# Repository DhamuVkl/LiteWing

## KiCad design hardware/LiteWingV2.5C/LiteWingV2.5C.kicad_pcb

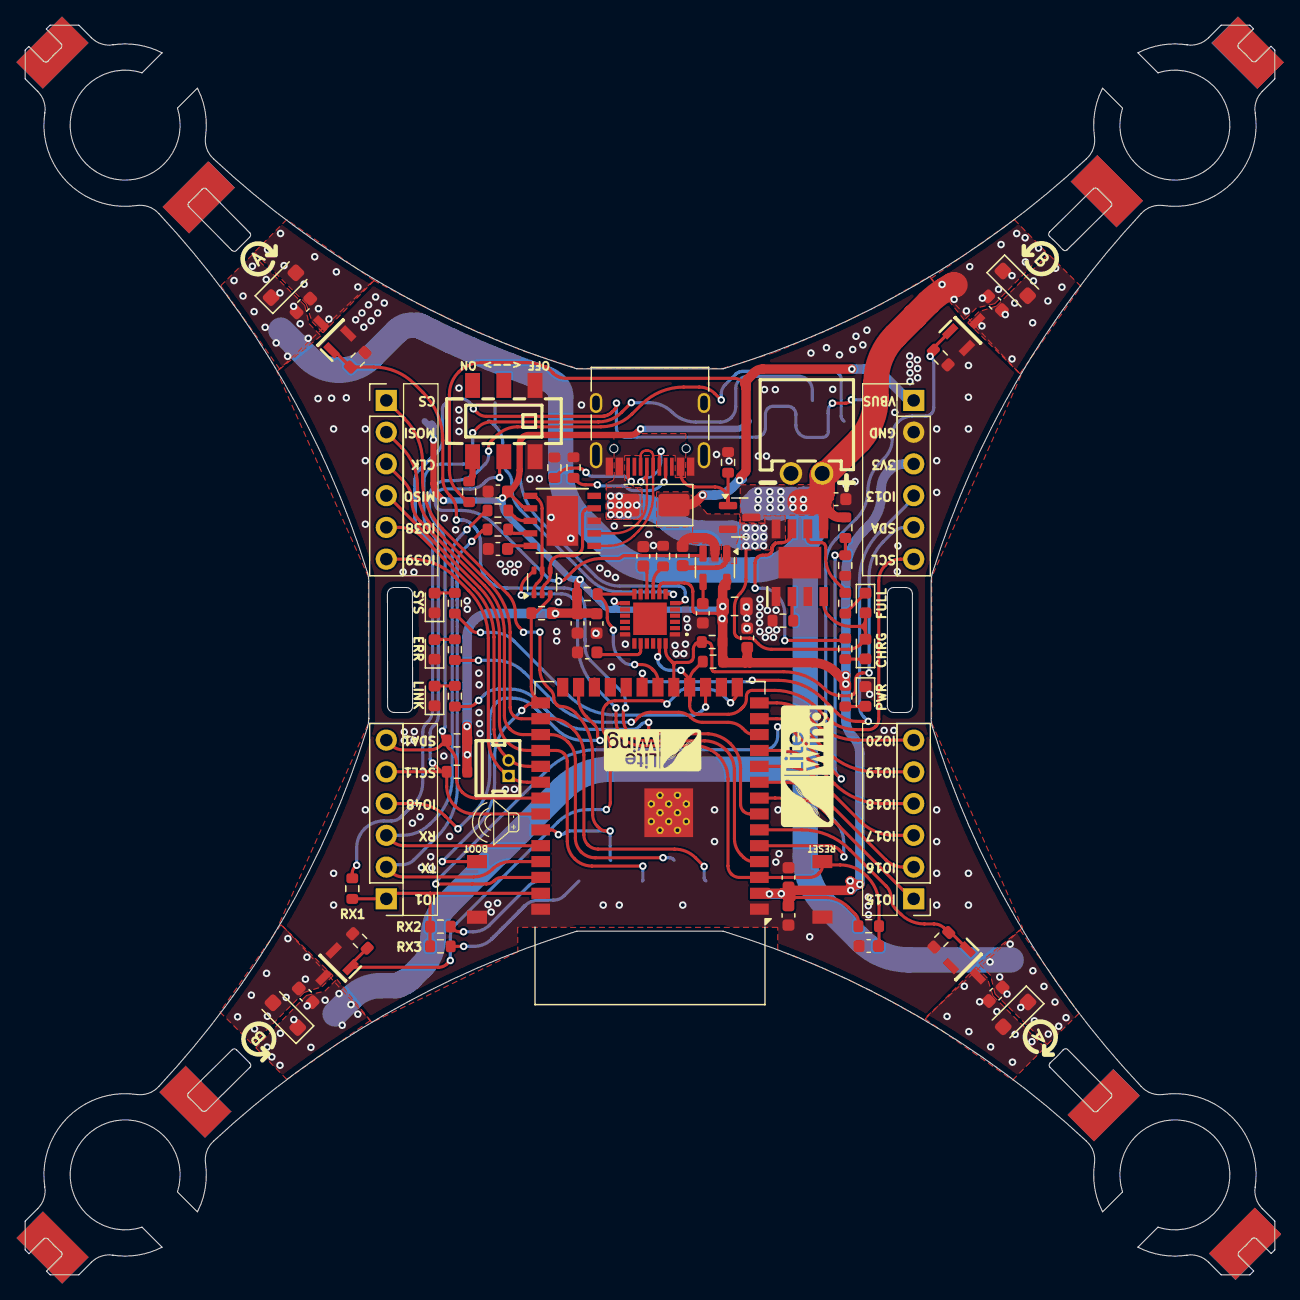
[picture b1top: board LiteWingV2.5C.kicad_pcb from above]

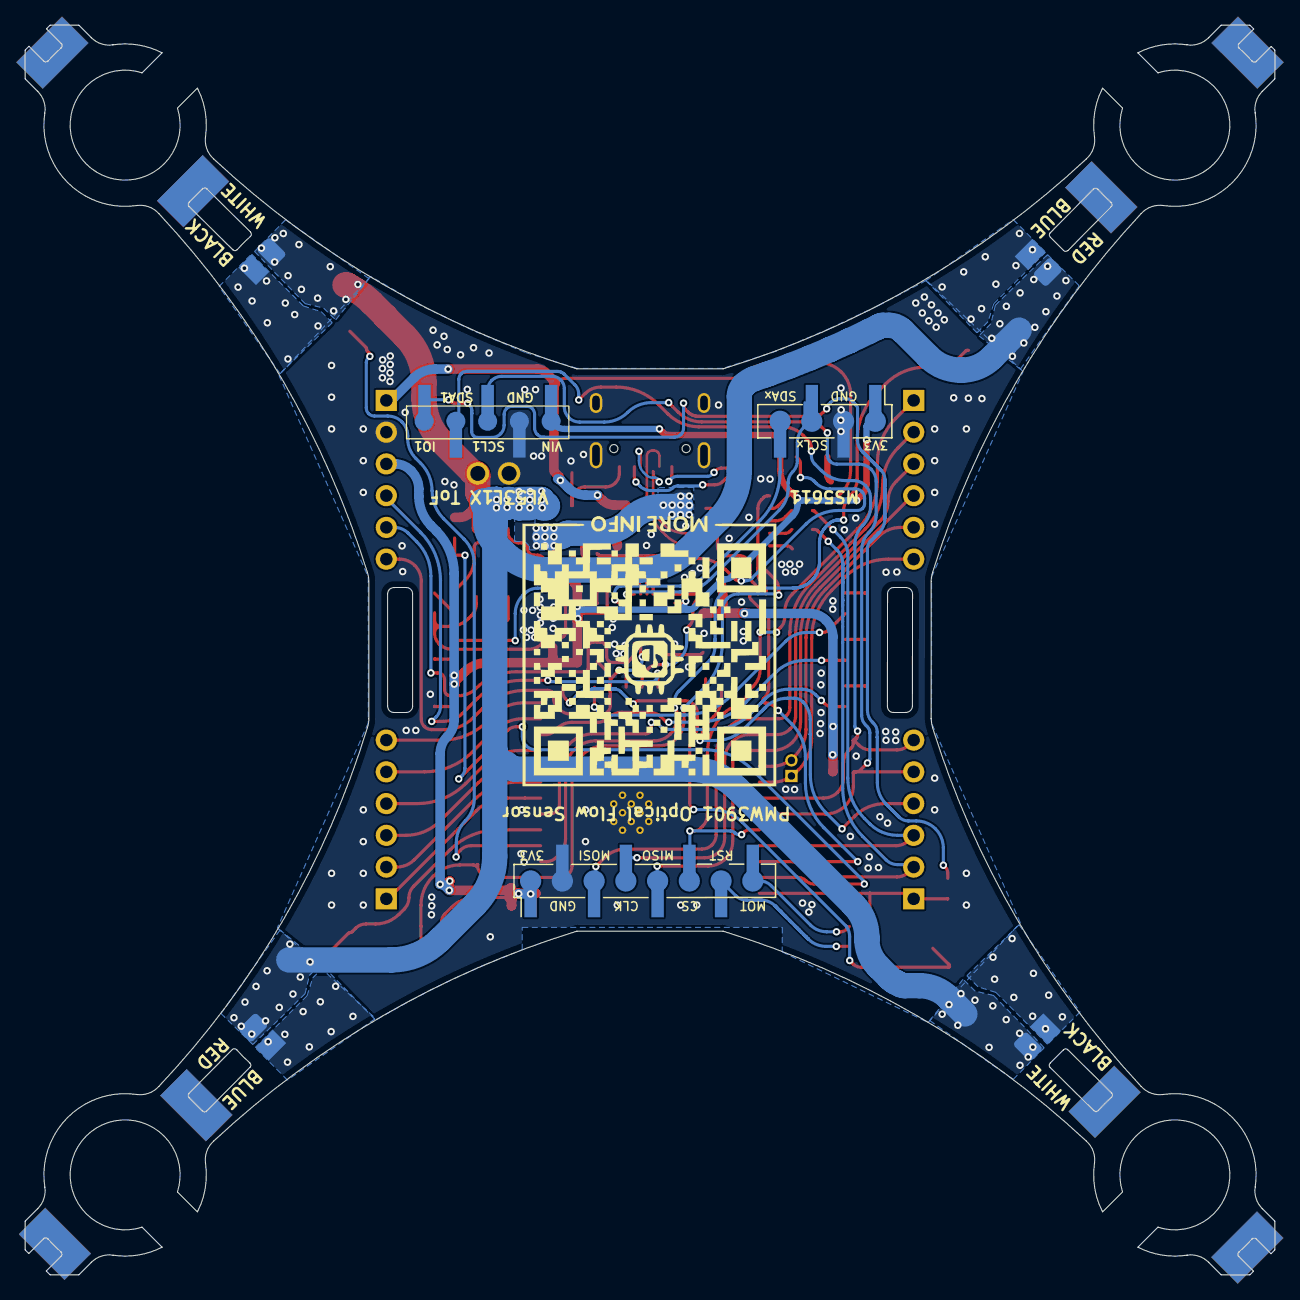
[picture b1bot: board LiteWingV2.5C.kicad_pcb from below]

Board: 2 copper layers, 100.0 x 100.0 mm, 87 parts (3 on the bottom side), 70 nets.

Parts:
C1, C4, C5, C12: 10uF; C_0603_1608Metric
C2: 470pF; C_0603_1608Metric
C3: 2.2uF; C_0805_2012Metric
C6, C7, C8, C10, C13, C14: 100nF; C_0603_1608Metric
C9: 2.2nf; C_0603_1608Metric
C11: 10nf; C_0603_1608Metric
C15, C16, C17, C18: 1uF; C_0603_1608Metric
D1: SS34; D_SMA
D2, D3, D4, D5: 1N4148W; D_SOD-123F
IC1: TP4056; SOIC127P600X175-9N
J1: USB_C_Receptacle_USB2.0; USB_C_Receptacle_HRO_TYPE-C-31-M-12
J2: JST XH 2P 2.50mm SMD Hoz; CONN-TH_2P-P2.50_XH-2AW
J3, J4, J5, J6: Conn_01x06; PinHeader_1x06_P2.54mm_Vertical
J7, J8, J9, J10: Conn_01x02_Female; JST_PH_B2B-PH-K_1x02_P2.00mm_Vertical
J11: Conn_01x09; PMW3901
J12: Conn_01x06; VL53L1X_BREAKOUT
J13: Conn_01x07; MS5611_Module
J14: Conn_01x02; CONN-TH_1.25T-2A_1.25T-2A
LED1, LED2, LED5: LED_Red; LED_0603_1608Metric
LED3, LED6: LED_Blue; LED_0603_1608Metric
LED4: LED_Green; LED_0603_1608Metric
R1, R2: 5.1K; R_0603_1608Metric
R3, R8, R26, R27: 100K; R_0603_1608Metric
R4: 470R; R_0603_1608Metric
R5: 1.2K; R_0603_1608Metric
R6, R7, R9, R10, R11, R12, R13: 1K; R_0603_1608Metric
R14, R16, R17, R18, R19, R20, R21, R22, R23, R24, R25: 10k; R_0603_1608Metric
R15: 4.7k; R_0603_1608Metric
R28, R29, R30: 0R; R_0603_1608Metric
SW1: MST22D18G2_125; SW-SMD_MST22D18G2
SW2, SW3: Tactile Switch 3x4x2; Tactile 3x4x2mm TS-A010
T1, T2, T3, T4: IRLML6344TRPBF; SOT95P237X112-3N
U1: AO3401A; SOT-23
U2: SPX3819M5-L-3-3/TR; SOT-23-5
U5: CH340K; ESSOP-10_3.9x4.9mm_P1.00mm
U6: 2N27002DW; SOT-363_SC-70-6
U7: MPU-6050; MPU6050
U8: ESP32-S3-WROOM-1

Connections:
+3V3: C3.1, C4.1, C7.1, C10.1, C11.1, C12.1, C13.1, J4.3, J11.1, J12.1, J13.1, R4.2, R14.2, R16.2, R17.2, R18.2, R19.2, R20.2, R21.2, U2.5 (OUT), U5.7 (VCC), U7.8 (VLOGIC), U7.13 (VDD), U8.2 (3V3)
+5V: D1.2 (A), IC1.4 (VCC), IC1.8 (CE), J1.A4 (VBUS), J1.A9 (VBUS), J1.B4 (VBUS), J1.B9 (VBUS), LED2.2 (A), LED3.2 (A), R3.1, U1.1 (G)
+BATT: C5.1, C15.1, C16.1, C17.1, C18.1, D2.1 (K), D3.1 (K), D4.1 (K), D5.1 (K), IC1.5 (BAT), J2.1, J7.1, J8.1, J9.1, J10.1, R26.1, U1.3 (D)
/ADC_BAT: R26.2, R27.1, U8.38 (IO2)
/AUXSCL: J13.3, U7.7 (AUX_CL)
/AUXSDA: J13.4, U7.6 (AUX_DA)
/BUZ1: J6.5, J14.2, U8.31 (IO38)
/BUZ2: J6.6, J14.1, U8.32 (IO39)
/CLK: J6.3, J11.4, U8.29 (IO36)
/CS: J6.1, J11.6, U8.35 (IO42)
/D+: J1.A6 (D+), J1.B6 (D+), U5.1 (D+)
/D-: J1.A7 (D-), J1.B7 (D-), U5.2 (D-)
/DTR: U5.4 (DTR), U6.2, U6.4
/EN: C14.1, R18.1, SW3.2, U6.6, U8.3 (EN)
/IO0: R19.1, SW2.2, U6.3, U8.27 (IO0)
/IO1: J5.1, R28.1, R29.1, R30.1, U8.39 (IO1)
/IO13: J4.4, U8.21 (IO13)
/IO15: J3.1, U8.8 (IO15)
/IO16: J3.2, U8.9 (IO16)
/IO17: J3.3, U8.10 (IO17)
/IO18: J3.4, U8.11 (IO18)
/IO19: J3.5, U8.13 (IO19)
/IO20: J3.6, U8.14 (IO20)
/IO48: J5.4, U8.25 (IO48)
/LDO_H: R8.2, SW1.3
/LED_BLUE: R13.2, U8.7 (IO7)
/LED_GREEN: R11.2, U8.17 (IO9)
/LED_RED: R12.2, U8.12 (IO8)
/MISO: J6.4, J11.5, U8.30 (IO37)
/MOSI: J6.2, J11.3, U8.28 (IO35)
/MOT_1: R22.2, T1.1 (G), U8.5 (IO5)
/MOT_2: R23.2, T2.1 (G), U8.6 (IO6)
/MOT_3: R24.2, T3.1 (G), U8.15 (IO3)
/MOT_4: R25.2, T4.1 (G), U8.4 (IO4)
/MPU_INT: R17.1, U7.12 (INT), U8.20 (IO12)
/RTS: U5.6 (RTS), U6.1, U6.5
/RX: J5.3, R10.1, U8.36 (RXD0)
/SCL: J4.6, R16.1, U7.23 (SCL), U8.18 (IO10)
/SCL1: J5.5, J12.3, R21.1, U8.34 (IO41)
/SDA: J4.5, R14.1, U7.24 (SDA), U8.19 (IO11)
/SDA1: J5.6, J12.4, R20.1, U8.33 (IO40)
/TX: J5.2, R9.1, U8.37 (TXD0)
GND: C1.2, C2.2, C3.2, C4.2, C5.2, C6.1, C7.2, C8.2, C9.2, C10.2, C11.2, C12.2, C13.2, C14.2, IC1.1 (TEMP), IC1.3 (GND), IC1.9 (EP), J1.A1 (GND), J1.A12 (GND), J1.B1 (GND), J1.B12 (GND), J1.S1 (SHIELD), J2.2, J4.2, J11.2, J12.2, J13.2, LED1.1 (K), LED4.1 (K), LED5.1 (K), LED6.1 (K), R1.2, R2.2, R3.2, R5.2, R15.1, R22.1, R23.1, R24.1, R25.1, R27.2, SW1.1, SW1.4, SW2.1, SW3.1, T1.2 (S), T2.2 (S), T3.2 (S), T4.2 (S), U2.2 (GND), U5.3 (GND), U5.11 (EP), U7.1 (CLKIN), U7.11 (FSYNC), U7.18 (GND), U8.1 (GND), U8.40 (GND), U8.41 (GND)
LDO_EN: SW1.2, U2.3 (EN)
unnamed: C15.2, D2.2 (A), J7.2, T1.3 (D)
unnamed: C16.2, D3.2 (A), J8.2, T2.3 (D)
unnamed: C17.2, D4.2 (A), J9.2, T3.3 (D)
unnamed: C18.2, D5.2 (A), J10.2, T4.3 (D)
unnamed: IC1.2 (PROG), R5.1
unnamed: IC1.7 (~CHRG), R6.2
unnamed: IC1.6 (~STDBY), R7.2
unnamed: J1.A5 (CC1), R2.1
unnamed: J1.B5 (CC2), R1.1
unnamed: J11.7, R29.2
unnamed: J11.8, R30.2
unnamed: J12.5, R28.2
unnamed: LED1.2 (A), R4.1
unnamed: LED2.1 (K), R6.1
unnamed: LED3.1 (K), R7.1
unnamed: LED4.2 (A), R11.1
unnamed: LED5.2 (A), R12.1
unnamed: LED6.2 (A), R13.1
unnamed: C2.1, U2.4 (BP)
unnamed: R9.2, U5.9 (RXD)
unnamed: R10.2, U5.8 (TXD)
unnamed: C6.2, U5.10 (V3)
unnamed: R15.2, U7.9 (AD0)
unnamed: C9.1, U7.20 (CPOUT)
unnamed: C8.1, U7.10 (REGOUT)
VBUS: C1.1, D1.1 (K), J4.1, R8.1, U1.2 (S), U2.1 (IN)

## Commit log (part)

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2025-10-27 #SYS_INI
2025-10-27 created driver for WS2812B NeoPixel LED's
2025-10-27 disabled position hold commander_mode to test the shield
2025-10-27 added neopixel.c in CMake
2025-10-27 tested the neopixel led function on main sys self check
2025-10-27 added COM port & flash type
2025-10-28 created dedicated crtp port for neopixel control
2025-10-28 initalized the neopixel_crtp on sys
2025-10-28 added neopixel_crtp to CMake build
2025-10-28 modified script to support neopixel in same udp
2025-10-28 test lib for neopixel crtp script
2025-10-29 #removed build files
2025-10-29 Added .gitignore to exclude build/ and other generated files
2025-10-29 added plot log view script
2025-10-29 modified script to include neopixel control
2025-10-29 modified git and vscode settings
2025-10-29 system: use vTaskDelay and stop neopixel blink after selftest (replace Python sleep)
2025-10-29 system: blink neopixel until CRTP client connects (use crtpIsConnected)
2025-10-29 removed cache files
2025-10-29 #rmd cache
2025-10-29 Start NeoPixel red blink in powerStop() and stop it in powerDistribution() only on transition. Add neopixel_blinking flag to avoid repeated timer allocations and reduce heap churn. fix(neopixel): bli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
2025-10-29 changed neopixel driver to option solid color sets
2025-10-29 add option to solid color in powerStop
2025-10-29 created a pattern generator script for position find
2025-10-29 pattern generator script pdf output
2025-10-29 settings.json change
2025-10-30 added aditional set pixel channel
2025-10-30 redefined script on neopixel implementation
2025-10-30 Stop tracking cache folder
2025-10-30 stablized the pixel functions
2025-10-30 Improved modularity by organizing helper functions and GUI components
2025-10-30 ui position fix
2025-10-30 fixed the issue in drone log and refactored the code
2025-10-30 improved position scaling issue
2025-10-30 added new ui layout and fixed position factor
2025-10-30 added wifi connection intication on neopixel leds
2025-10-31 rearraged the neopixel intialize sequence
2025-10-31 created a drone maneuver logic
2025-10-31 improved neopixel fuctionality
2025-10-31 fixed the orientation and flight stablity
2025-10-31 resolved access local variable maneuver active
2025-10-31 #onprocress
2025-10-31 improved ui layout and added the joystick control but need some correction in joystick function
2025-11-01 fixed a issue in battery reading on each flight startup
2025-11-01 testing drone maneuver control fuction
2025-11-01 fixed flight control thread accesing waypoint local variable
2025-11-03 #git change
2025-11-03 fixed minor bug in sensor test function
2025-11-03 rollbacked sensor validation checks
2025-11-03 fixed another bug in kp duplication on pid controls
2025-11-03 Added addtional output log window for better troubleshooting
2025-11-03 foundout and fixed a bug in a joystick keypress also changed the joystick control from position based to velocity based in final swaped the joystick keys and added aditional emergency stop button on 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
2025-11-03 fixed the variable shadowing between local and global variables in joystick position hold
2025-11-04 removed some replicating less used task in ui
2025-11-04 resolved the position hold mode in joystick control and added the option to switch between orgin and current position to hold
2025-11-04 resolving the bug in a current position hold joystick control by adding predictive target point and pid correction reset to prevent overshoot from release point
2025-11-04 fixing issue on velocities didnt match with momentum and sensor coordinate system
2025-11-04 #git change markdown
2025-11-04 changing the shape maneuver to velocity based control instead of pid position correction
2025-11-05 #ongoing process: Update waypoint timeout and corner pause duration; enhance square maneuver logging and control logic
2025-11-05 Add position reset function to prevent sensor drift during tracking
2025-11-05 Enhance logging functionality by adding optional logger parameter to various functions for improved error handling and output control
2025-11-05 Add output log saving functionality and clear output on new runs
2025-11-05 Add debug mode toggle and reorganize sensor logging checkbox layout
2025-11-05 Implement safety checks for position integration reset and enhance position tracking initialization
2025-11-05 Add safety checks for position integration reset before takeoff
2025-11-05 Add height sensor safety checks during takeoff and stabilization phases
2025-11-05 Refactor height sensor safety checks during takeoff to use a constant for minimum height change and enhance logging for sensor validation
2025-11-05 Implement global logging mechanism to redirect messages to GUI output and replace print statements with log calls
2025-12-03 Refactor _Packet class in NeoPixel test to improve data handling and validation
2025-12-03 Refactor NeoPixel
2025-12-03 NeoPixel blinking functionality to support individual pixel control
2025-12-03 fix: updated neopixelSetPixelColor() so it frees and invalidates the s_items buffer after changing a pixel.
2025-12-03 fix Inverted X axis in optical flow calculations
2025-12-03 Refactor optical flow calculations and enhance documentation for clarity
2025-12-03 Enhance documentation and comments in height sensor, IMU, and NeoPixel scripts for clarity and maintainability
2025-12-10 feat: Implement standalone dead reckoning joystick control script for drone operation.
2025-12-10 feat: Introduce new standalone script for dead reckoning joystick control of a drone with a Tkinter GUI.
2025-12-12 feat: Add standalone dead reckoning optical position hold script.
2025-12-12 feat: Add new Python scripts for dead reckoning, optical flow position hold, joystick control, and maneuvers.
2025-12-12 feat: implement dead reckoning flight stabilization and maneuver control for Crazyflie drones
2025-12-15 feat: Added comments for IMU and optical flow sensors with live data visualization.
2025-12-15 refactor: Add dead reckoning scripts comment for flight stabilization, optical position hold, maneuvers, and joystick control.
2025-12-17 feat: corrected the config on dead reckoning scripts for joystick control, maneuvers, and optical position hold, and update gitignore.
2025-12-18 feat: Add option to switch between hover and hold to hover and land
2025-12-19 feat: Implement joystick control with automatic position hold.
2025-12-20 fix: tunned the pid and drift rate to improve stability
2025-12-23 Fix: corrected the background thread issue in sensor readings
2025-12-23 Feat: fixed the drone drift compensation control without trim corrections
2025-12-23 Fix: integrate position update reset interval
2025-12-23 Fix: improved the drone oscillation
2025-12-23 Feat: add a LiteWing logo
2025-12-23 fix: ongoing process in joystick control
2025-12-23 test: added watchdog timmer safty system
2025-12-23 fix: Optimized the UI scaling, buffer and thread
2025-12-23 fix: removed driver initialization on main thread
2025-12-23 feat: add option to disable logs
2025-12-23 fix: fixed joystick throttle counter reset issue
2025-12-26 Fix: fixed the height bouncing effect in position hold
2025-12-26 TempFix: disabled height saftey function (robu batt didnt work)
2025-12-26 TempFix: fixed maneuver control logic
2025-12-26 fixed hover duration interface in maneuver logic
2025-12-26 Fix: fixed coordinate calculation in maneuer logic
2025-12-26 Fix: fixed the square pattern movement logic
2025-12-26 TFix: fixed auto-trim correction in maneuver control
2025-12-26 Feat: add esc key as emergency stop switch
2025-12-27 changed the control correction on takeoff
2025-12-27 Fix: fixed the joystick correction parameter
2025-12-27 #PID-Doc
2025-12-27 Feat: add zaxis pid tunning capabilities
2025-12-27 feat: added option to disable the ramp takeoff function
2025-12-27 TFix: fixed tof value when error occurs in measurement to prevent data to stream
2025-12-29 fix: moved out legends on position map in gui
2025-12-29 Fix: resolved integrated position reset issue in maneuver control logic
2026-01-05 test script
2026-01-05 feat: add tof plot to view raw values
2026-01-06 feat: add hardware glitch filter in i2c line
2026-01-06 fix: add a safty check on NACK to ignore uncompleted packets
2026-01-06 Feat: 1. Integrated the MS5611 Barometric pressure sensor and implemented the processing logic , 2. Fixed the ms5611 connection check placeholder block, 3. detached the ms5611 from slave configuratio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
2026-01-06 refactor the comment on unused function
2026-01-10 fix: improved stability without trim values
2026-01-10 fix: plot scalling
2026-01-10 MS5611 Barometer test script
2026-02-16 feat: Add LiteWing Python library for flight stabilization and control, including core modules and examples.
2026-02-17 Rearraged
2026-02-17 feat: Initialize the LiteWing Python library, including PID control, flight engine, drone modules, tests, and examples.
2026-02-17 feat: Add LiteWing Python library including core drone control, sensor data access, and initial examples.
2026-02-17 Fixed sensor attribute assignement on height
2026-02-17 feat: Add Level 1 sensor reading examples for battery, height, position, velocity, and all sensors, and update the README.
2026-02-17 feat: Add IMU sensor data to the LiteWing library, including logging setup and usage examples.
2026-02-17 feat: Add `gui` module with live matplotlib dashboards for drone sensor data visualization including height, IMU, velocity, and battery, along with corresponding examples.
2026-02-17 feat: Add `litewing.gui` module for live sensor plotting and include a position plot example.
2026-02-17 feat: Add LiteWing drone control library and level 2 flight examples including LED control, basic flight, tuning, movement commands, and data logging.
2026-02-23 feat: add Changed MS5611 sensor HAL implementation and sel test in initialization
2026-02-23 disabled unused barometer function
2026-02-23 fixed direction logic and velocity speed set value application
2026-02-23 feat: Add Level 3 examples demonstrating advanced drone control, tuning, and navigation capabilities.
2026-02-23 restructured the scripts
2026-02-23 docs: Add API reference and quick reference documentation for the litewing library.
2026-02-23 feat: add system wide emergency shutdown key
2026-02-23 feat: add check_sensor_health i2c device check method and arm() guard
2026-02-23 add basic mode to control drone without Flight Positioning Module
2026-02-23 renamed some function calls
2026-02-24 feat: Add VL53L1X Time-of-Flight distance sensor driver with auto distance mode switching and noise modeling.
2026-02-24 fixed the timing budget for long mode and reconfigured RangeStatus Filtering
2026-02-24 reconfigured threshold
2026-02-24 feat: improved landing phase with position hold active
2026-02-24 add additional dependencies
2026-02-24 feat: added UDP port in URI
2026-02-24 updated the toml
2026-02-25 reconfigured .toml to support only on python 3.11 also created a batch script for library installation (currently git auto download didnt work)
2026-02-25 feat: Add Windows installer script to automate LiteWing library and Python 3.11 setup, alongside pyproject.toml.
2026-02-25 feat: Add Linux installer script to automate LiteWing library and Python 3.11 setup
2026-02-25 updated the Linux installer script run guide to automate LiteWing library
2026-02-25 chore: prepare litewing-library for standalone repo - Add .gitignore (exclude level_0, cache, build artifacts) - Update pyproject.toml URLs to DhamuVkl/LiteWing-Library - Remove level_0 from tracking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
